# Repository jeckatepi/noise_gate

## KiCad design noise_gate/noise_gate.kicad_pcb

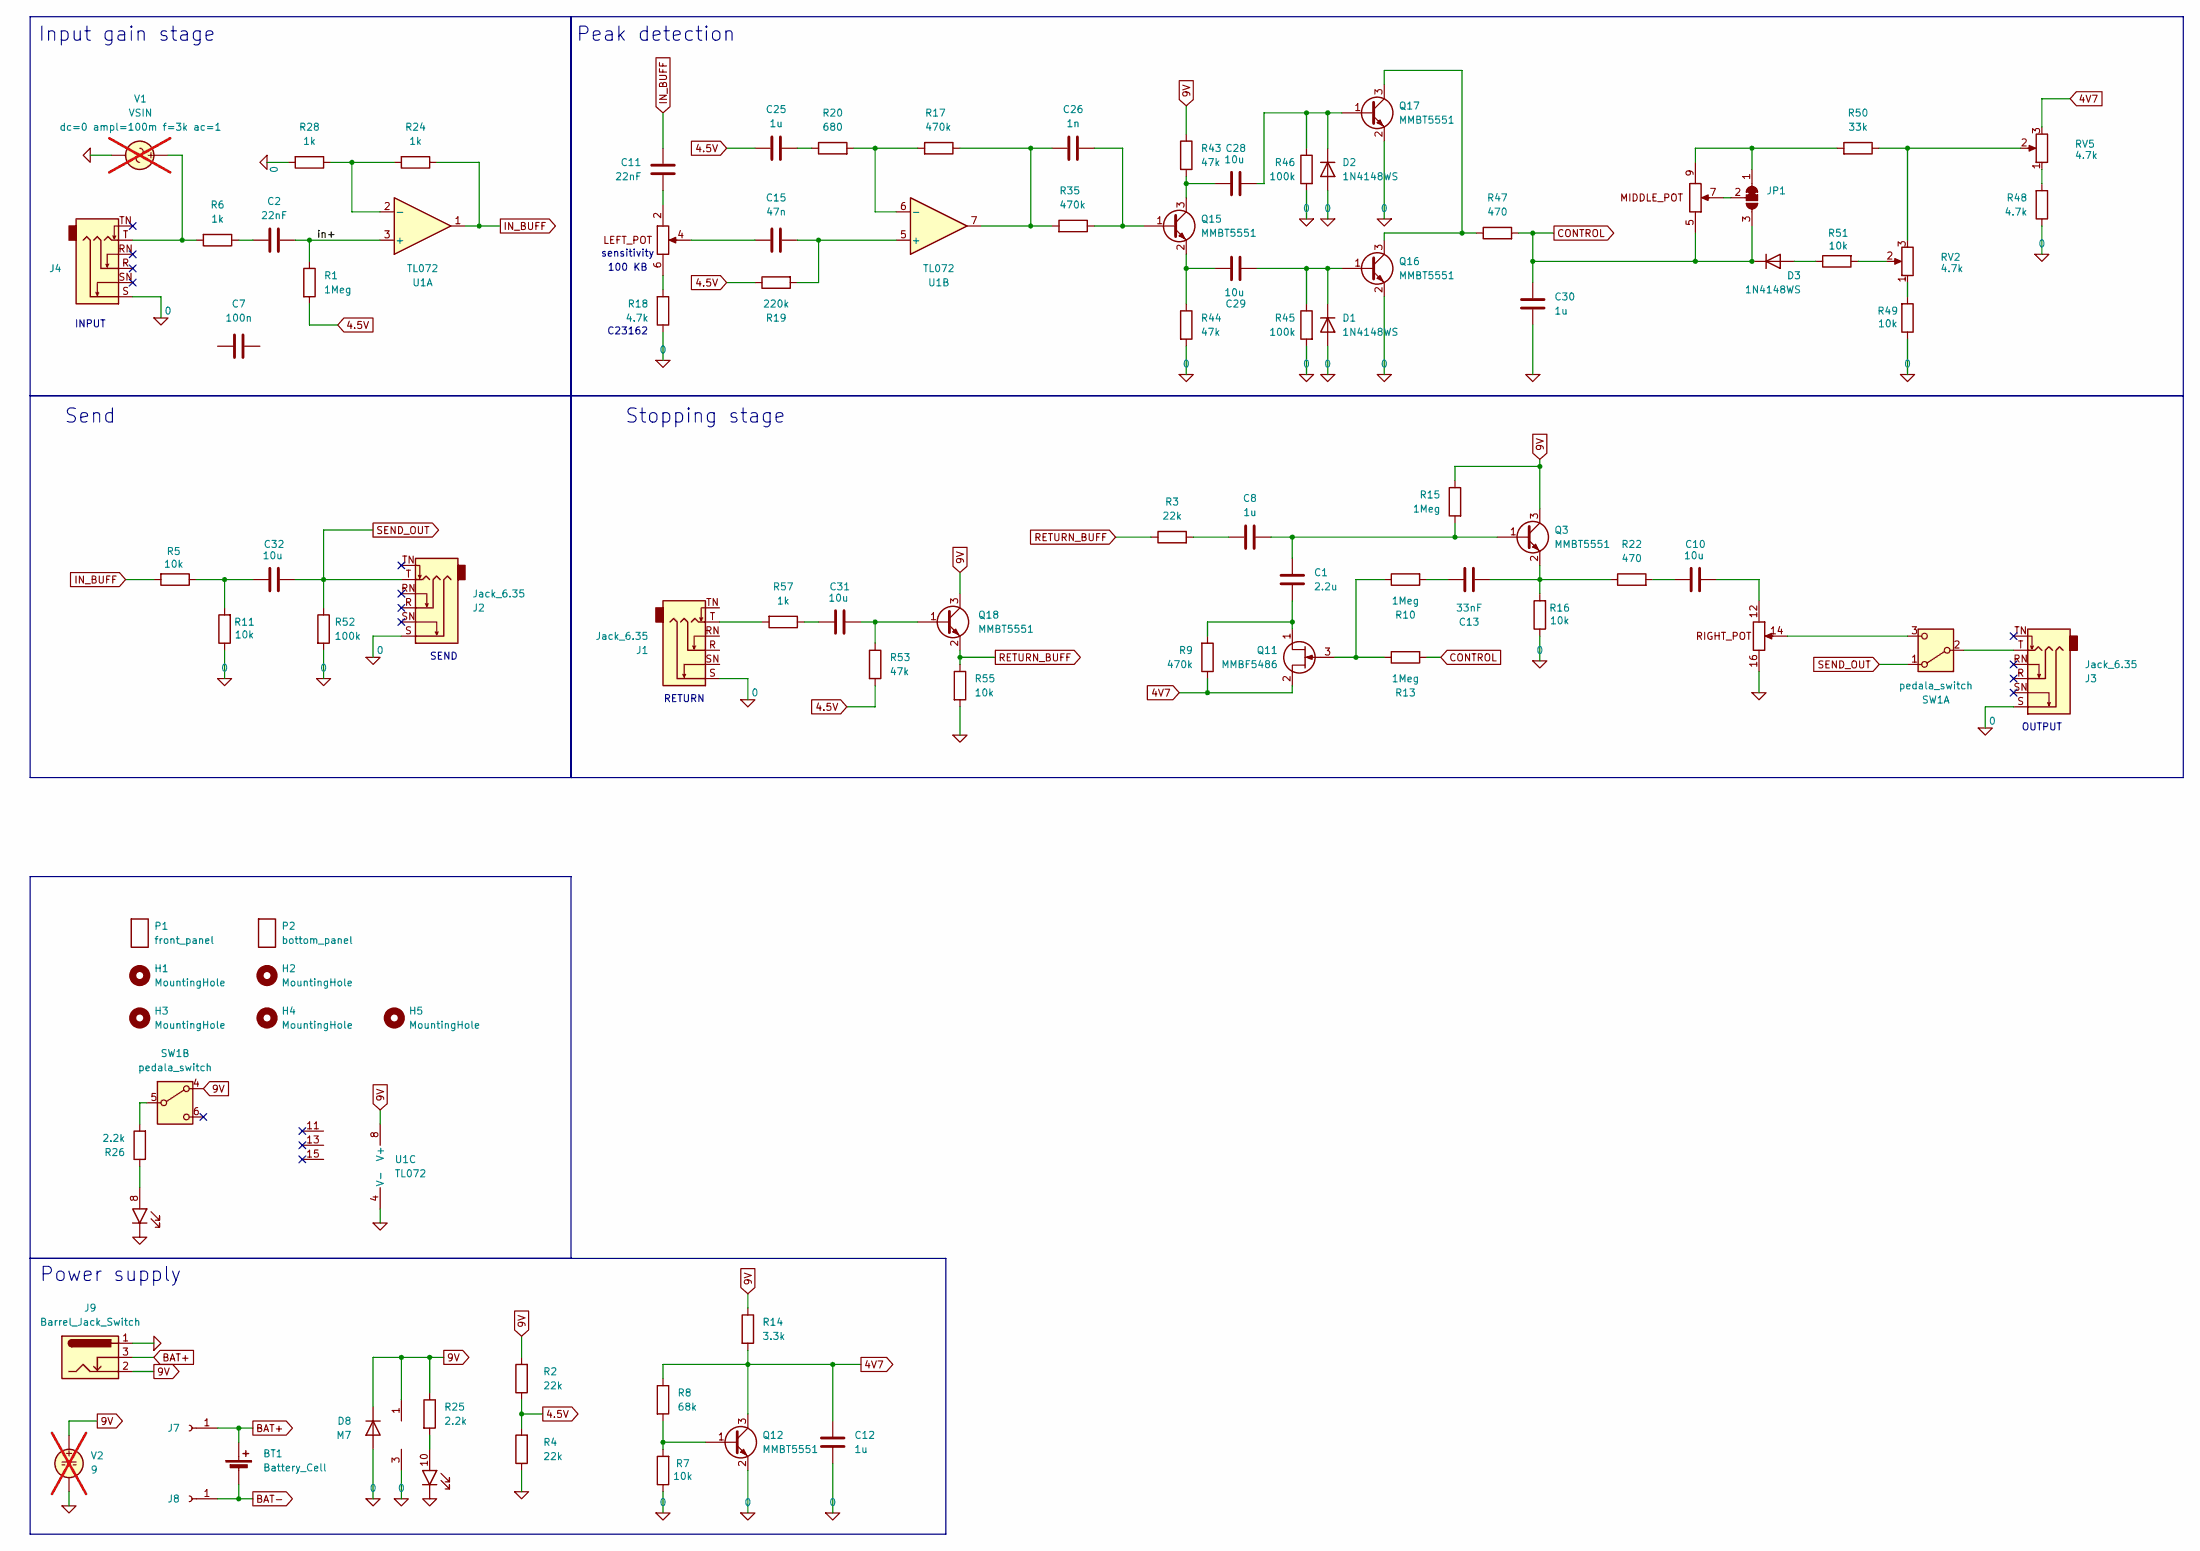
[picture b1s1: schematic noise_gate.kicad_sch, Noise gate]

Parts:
BT1: Battery_Cell; BatteryHolder_Eagle_12BH611-GR
C1: 2.2u; C_0603_1608Metric_Pad1.08x0.95mm_HandSolder; LCSC C21122
C2, C11: 22nF; C_0603_1608Metric_Pad1.08x0.95mm_HandSolder; LCSC C21122
C7: 100n; C_0603_1608Metric_Pad1.08x0.95mm_HandSolder; LCSC C14663
C8, C12, C25, C30: 1u; C_0603_1608Metric_Pad1.08x0.95mm_HandSolder; LCSC C15849
C10, C28, C29, C31, C32: 10u; C_0603_1608Metric_Pad1.08x0.95mm_HandSolder; LCSC C96446
C13: 33nF; C_0603_1608Metric_Pad1.08x0.95mm_HandSolder; LCSC C1614
C15: 47n; C_0603_1608Metric_Pad1.08x0.95mm_HandSolder; LCSC C1622
C26: 1n; C_0603_1608Metric_Pad1.08x0.95mm_HandSolder; LCSC C1588
D1, D2, D3: 1N4148WS; D_SOD-323; LCSC C2128
D8: M7; D_SMA; LCSC C95872
H1, H2, H3, H4, H5: MountingHole; M3_hole_with_spacer
J1, J2, J3, J4: Jack_6.35; Jack_6.35mm
J6: top_panel_connector; IDC-Header_2x08_P2.54mm_Vertical
J7, J8: Conn_01x01_Socket; TestPoint_THTPad_D2.5mm_Drill1.2mm
J9: Barrel_Jack_Switch; BarrelJack
JP1: SolderJumper_3_Bridged12; SolderJumper-3_P1.3mm_Bridged12_Pad1.0x1.5mm
P1: front_panel; front_plate
P2: bottom_panel; bottom_plate
Q3, Q12, Q15, Q16, Q17, Q18: MMBT5551; SOT-23; LCSC C2145
Q11: MMBF5486; SOT-23
R1, R10, R13, R15: 1Meg; R_0603_1608Metric_Pad0.98x0.95mm_HandSolder; LCSC C25819
R2, R3, R4: 22k; R_0603_1608Metric_Pad0.98x0.95mm_HandSolder; LCSC C31850
R5, R7, R11, R16, R49, R51, R55: 10k; R_0603_1608Metric_Pad0.98x0.95mm_HandSolder; LCSC C25804
R6, R24, R28, R57: 1k; R_0603_1608Metric_Pad0.98x0.95mm_HandSolder; LCSC C21190
R8: 68k; R_0603_1608Metric_Pad0.98x0.95mm_HandSolder; LCSC C23231
R9, R17, R35: 470k; R_0603_1608Metric_Pad0.98x0.95mm_HandSolder; LCSC C23178
R14: 3.3k; R_0603_1608Metric_Pad0.98x0.95mm_HandSolder; LCSC C22978
R18, R48: 4.7k; R_0603_1608Metric_Pad0.98x0.95mm_HandSolder; LCSC C23162
R19: 220k; R_0603_1608Metric_Pad0.98x0.95mm_HandSolder; LCSC C22961
R20: 680; R_0603_1608Metric_Pad0.98x0.95mm_HandSolder; LCSC C23228
R22, R47: 470; R_0603_1608Metric_Pad0.98x0.95mm_HandSolder; LCSC C23179
R25, R26: 2.2k; R_0603_1608Metric_Pad0.98x0.95mm_HandSolder; LCSC C4190
R43, R44, R53: 47k; R_0603_1608Metric_Pad0.98x0.95mm_HandSolder; LCSC C25819
R45, R46, R52: 100k; R_0603_1608Metric_Pad0.98x0.95mm_HandSolder; LCSC C25803
R50: 33k; R_0603_1608Metric_Pad0.98x0.95mm_HandSolder; LCSC C4216
RV2, RV5: 4.7k; Potentiometer_Bourns_3296W_Vertical
SW1: pedala_switch; foot_switch_tht_no_pad
U1: TL072
V1: VSIN; not fitted
V2: 9; not fitted

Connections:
0: C12.1, C30.1, D1.2 (A), D2.2 (A), D8.2 (A), J1.S, J2.S, J3.S, J4.S, J6.3 (GND), J6.16, J9.1, Q12.2 (E), Q16.2 (E), Q17.2 (E), R4.1, R7.1, R11.1, R16.1, R18.1, R28.2, R44.2, R45.2, R46.2, R48.1, R49.1, R52.2, R55.2, U1.4 (V-), V1.2, V2.2; also elsewhere on the board
4.5V: C25.1, R1.2, R2.1, R4.2, R19.1, R53.2
4V7: C12.2, Q11.2 (S), Q12.3 (C), R8.1, R9.1, R14.2, RV5.3
9V: D8.1 (K), J6.1 (VCC), J9.2, Q3.3 (C), Q18.3 (C), R2.2, R14.1, R15.1, R25.1, R43.1, SW1.4 (A), U1.8 (V+), V2.1; also elsewhere on the board
/in+: C2.2, R1.1, U1.3 (+)
BAT+: BT1.1 (+), J7.1, J9.3
BAT-: BT1.2 (-), J8.1
CONTROL: C30.2, D3.1 (K), J6.5, JP1.3 (B), R13.2, R47.2
IN_BUFF: C11.2, R5.2, R24.1, U1.1
unnamed: C2.1, R6.1
unnamed: C8.1, R3.2
unnamed: C10.1, R22.2
unnamed: C13.1, R10.2
unnamed: C25.2, R20.1
unnamed: C26.1, R17.1, R35.2, U1.7
unnamed: C31.1, R57.1
unnamed: C32.1, R5.1, R11.2
unnamed: C29.2, D1.1 (K), Q16.1 (B), R45.1
unnamed: C28.2, D2.1 (K), Q17.1 (B), R46.1
unnamed: D3.2 (A), R51.1
unnamed: J1.T, R57.2
unnamed: J4.T, R6.2, V1.1
unnamed: C11.1, J6.2
unnamed: C15.1, J6.4
unnamed: J6.6, R18.2
unnamed: J6.7, JP1.2 (C)
unnamed: J6.9, JP1.1 (A), R50.2
unnamed: C10.2, J6.12
unnamed: J6.14, SW1.3 (C)
unnamed: J6.8, R26.1
unnamed: J6.10, R25.2
unnamed: C1.2, C8.2, Q3.1 (B), R15.2
unnamed: C13.2, Q3.2 (E), R16.2, R22.1
unnamed: C1.1, Q11.1 (D), R9.2
unnamed: Q11.3 (G), R10.1, R13.1
unnamed: Q12.1 (B), R7.2, R8.2
unnamed: C26.2, Q15.1 (B), R35.1
unnamed: C28.1, Q15.3 (C), R43.2
unnamed: C29.1, Q15.2 (E), R44.1
unnamed: Q16.3 (C), Q17.3 (C), R47.1
unnamed: C31.2, Q18.1 (B), R53.1
unnamed: R48.2, RV5.1
unnamed: R49.2, RV2.1
unnamed: R50.1, RV2.3, RV5.2
unnamed: R51.2, RV2.2
unnamed: J3.T, SW1.2 (B)
unnamed: R26.2, SW1.5 (B)
unnamed: R24.2, R28.1, U1.2 (-)
unnamed: C15.2, R19.2, U1.5 (+)
unnamed: R17.2, R20.2, U1.6 (-)
RETURN_BUFF: Q18.2 (E), R3.1, R55.1
SEND_OUT: C32.2, J2.T, R52.1, SW1.1 (A)

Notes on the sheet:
Peak detection
sensitivity
RETURN
INPUT
SEND
Input gain stage
C23162
100 KB
Send
Stopping stage
Power supply
OUTPUT

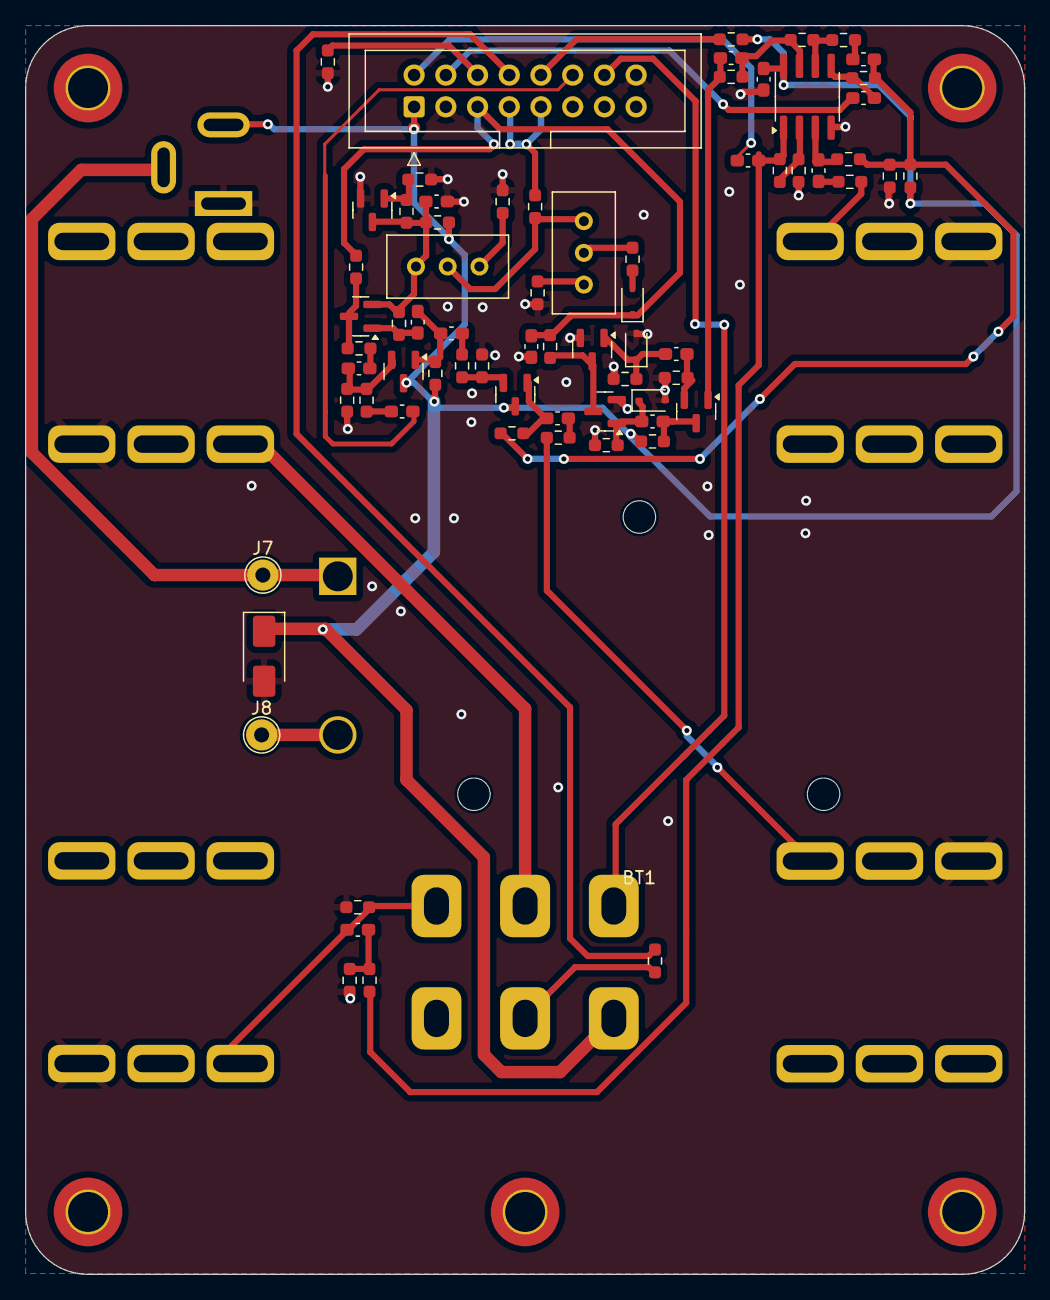
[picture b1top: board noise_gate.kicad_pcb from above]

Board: 2 copper layers, 80.0 x 100.0 mm, 86 parts (1 on the bottom side), 52 nets.

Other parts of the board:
C33: 1u; C_0603_1608Metric_Pad1.08x0.95mm_HandSolder

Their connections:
0: C33.1; also elsewhere on the board
9V: C33.2; also elsewhere on the board
